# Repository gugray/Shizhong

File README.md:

# Remarkably Accurate Quartz Clock

This repository has all the code and design files for the Remarkably Accurate Quartz Clock
[documented on Hackaday](https://hackaday.io/project/190063-remarkably-accurate-quartz-clock).

Can I use cheap, everyday components and build a quartz clock that beats specialized RTCs and matches the best commercial timepieces? Let's find out!

32kHz quartz crystals typically have a ±20ppm (parts per million) frequency tolerance, which translates to drift potentially in excess of 10 minutes per year. Specialized RTCs like DS3231 promise ±2ppm, or about ±1 minute per year.

RAQC aims for drift below 10 seconds per year. To achieve this, it implements fine-grained frequency correction in software. It has a screen to adjust time with subsecond precision, and it measures the temperature at 10-minute intervals to compensate for dynamic drift. After calibrating repeatedly at incresingly long intervals, RAQC knows the crystal's static error with a 0.01ppm precision.

Energy-saving programming techniques and a low-power LCD display keep the clock's current draw under 15μA, promising 1.5 years of uptime on a CR2032 coin cell.

## Electronics

The KiCad 5.1.9 schematic and PCB are in [/electronics](electronics). The ZIP file there is the Gerber export that I submitted to the PCB fab.

## Laser-cut frame

The frame is laser-cut from 3mm acryclic; the top and bottom covers are 1mm transparent acrylic. The front panel with the engraved overview of the clock's menu is laser-cut from 2mm birch.
The vector files for this are in [/design](design). The .ai file is the original, but I included a version re-saved as Inkscape .svg as well.

## Source code

The source code is in [/code/board](code/board). I developed it using the [PlatformIO extension](https://platformio.org/install/ide?install=vscode) for Visual Studio Code, so if you want to explore the code and build it yourself, that might be the easiest way to get started. The code uses the Arduino framework. It has only one dependency, the Wire library for I2C communication.

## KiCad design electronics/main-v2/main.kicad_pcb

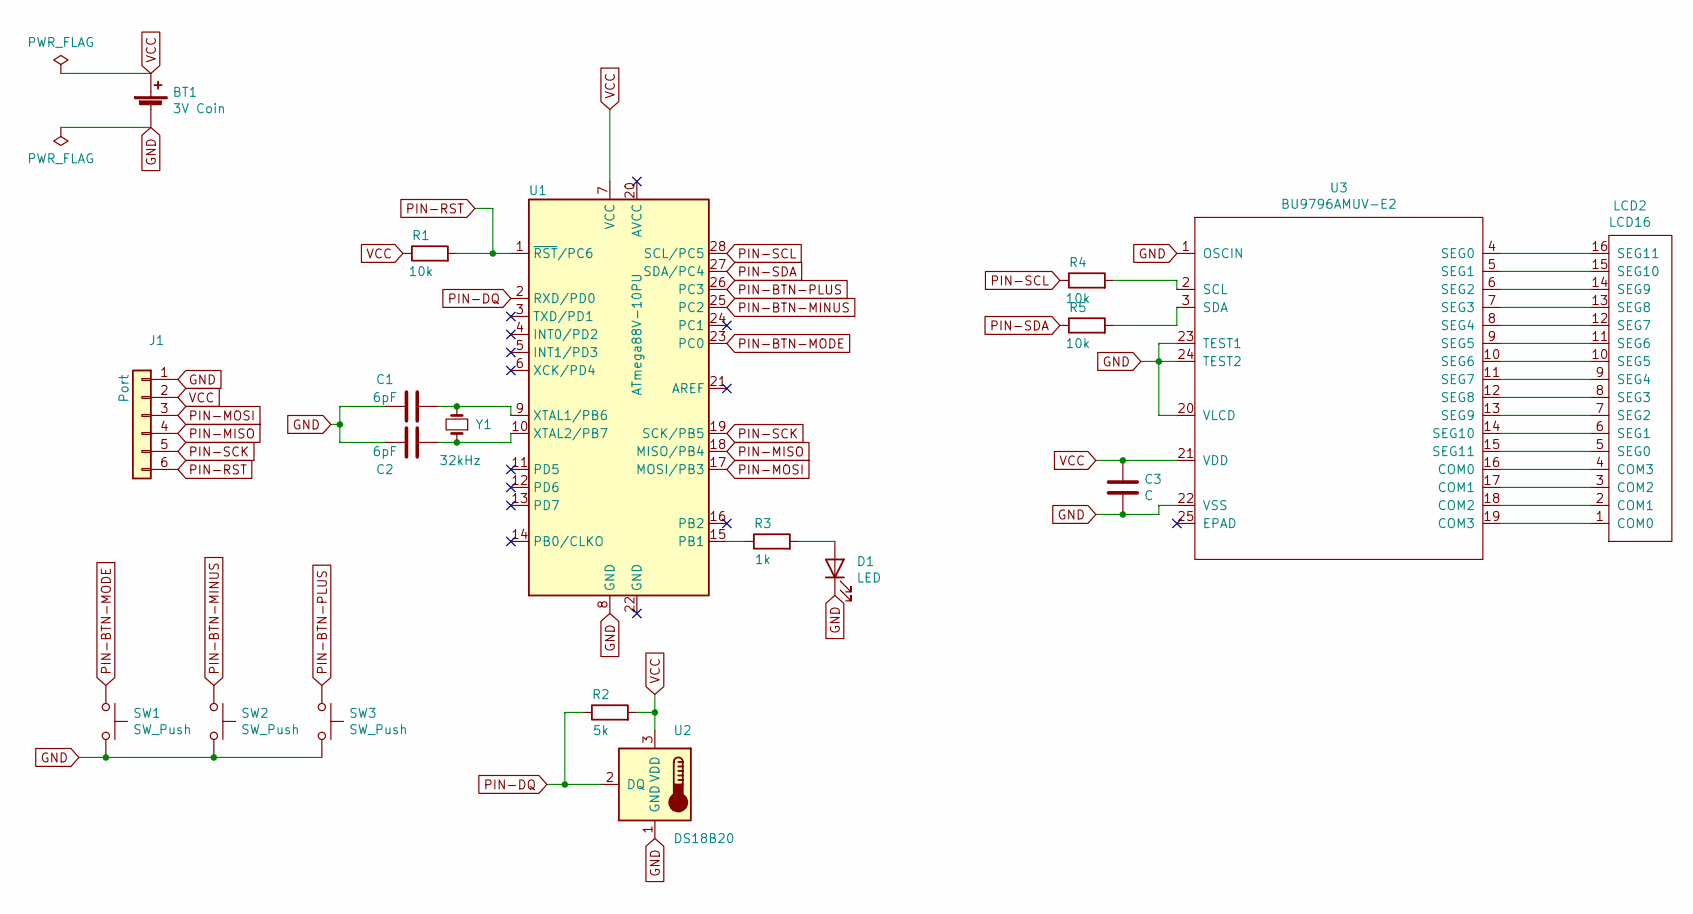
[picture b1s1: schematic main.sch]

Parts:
BT1: 3V Coin; BatteryHolder_Keystone_3002_1x2032
C1, C2: 6pF; R_Axial_DIN0204_L3.6mm_D1.6mm_P2.54mm_Vertical
C3: C; C_0603_1608Metric
D1: LED; LED_D2.0mm_W4.0mm_H2.8mm_FlatTop
J1: Port; PinHeader_1x06_P2.54mm_Vertical
LCD2: LCD16; LCD16-TN6
R1, R4, R5: 10k; R_Axial_DIN0207_L6.3mm_D2.5mm_P10.16mm_Horizontal
R2: 5k; R_Axial_DIN0207_L6.3mm_D2.5mm_P10.16mm_Horizontal
R3: 1k; R_Axial_DIN0207_L6.3mm_D2.5mm_P10.16mm_Horizontal
SW1, SW2, SW3: SW_Push; PushButton5mm
U1: ATmega88V-10PU; DIP-28_W7.62mm
U2: DS18B20; TO-92_Inline_Wide
U3: BU9796AMUV-E2; VQFN-24-1EP_4x4mm_P0.5mm_EP2.45x2.45mm
Y1: 32kHz; Crystal_C38-LF_D3.0mm_L8.0mm_Horizontal

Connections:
GND: BT1.2 (-), C1.1, C2.1, C3.2, D1.1 (K), J1.1, SW1.2, SW2.2, SW3.2, U1.8 (GND), U2.1 (GND), U3.1 (OSCIN), U3.20 (VLCD), U3.22 (VSS), U3.23 (TEST1), U3.24 (TEST2)
unnamed 1: C1.2, U1.9 (XTAL1/PB6), Y1.2; also elsewhere on the board
unnamed 2: C2.2, U1.10 (XTAL2/PB7), Y1.1; also elsewhere on the board
unnamed: D1.2 (A), R3.2
unnamed: LCD2.1 (COM0), U3.19 (COM3)
unnamed: LCD2.2 (COM1), U3.18 (COM2)
unnamed: LCD2.3 (COM2), U3.17 (COM1)
unnamed: LCD2.4 (COM3), U3.16 (COM0)
unnamed: LCD2.5 (SEG0), U3.15 (SEG11)
unnamed: LCD2.6 (SEG1), U3.14 (SEG10)
unnamed: LCD2.7 (SEG2), U3.13 (SEG9)
unnamed: LCD2.8 (SEG3), U3.12 (SEG8)
unnamed: LCD2.9 (SEG4), U3.11 (SEG7)
unnamed: LCD2.10 (SEG5), U3.10 (SEG6)
unnamed: LCD2.11 (SEG6), U3.9 (SEG5)
unnamed: LCD2.12 (SEG7), U3.8 (SEG4)
unnamed: LCD2.13 (SEG8), U3.7 (SEG3)
unnamed: LCD2.14 (SEG9), U3.6 (SEG2)
unnamed: LCD2.15 (SEG10), U3.5 (SEG1)
unnamed: LCD2.16 (SEG11), U3.4 (SEG0)
unnamed: R3.1, U1.15 (PB1)
unnamed: R4.2, U3.2 (SCL)
unnamed: R5.2, U3.3 (SDA)
PIN-BTN-MINUS: SW2.1, U1.25 (PC2)
PIN-BTN-MODE: SW1.1, U1.23 (PC0)
PIN-BTN-PLUS: SW3.1, U1.26 (PC3)
PIN-DQ: R2.1, U1.2 (RXD/PD0), U2.2 (DQ)
PIN-MISO: J1.4, U1.18 (MISO/PB4)
PIN-MOSI: J1.3, U1.17 (MOSI/PB3)
PIN-RST: J1.6, R1.2, U1.1 (~RST~/PC6)
PIN-SCK: J1.5, U1.19 (SCK/PB5)
PIN-SCL: R4.1, U1.28 (SCL/PC5)
PIN-SDA: R5.1, U1.27 (SDA/PC4)
VCC: BT1.1 (+), C3.1, J1.2, R1.1, R2.2, U1.7 (VCC), U2.3 (VDD), U3.21 (VDD)

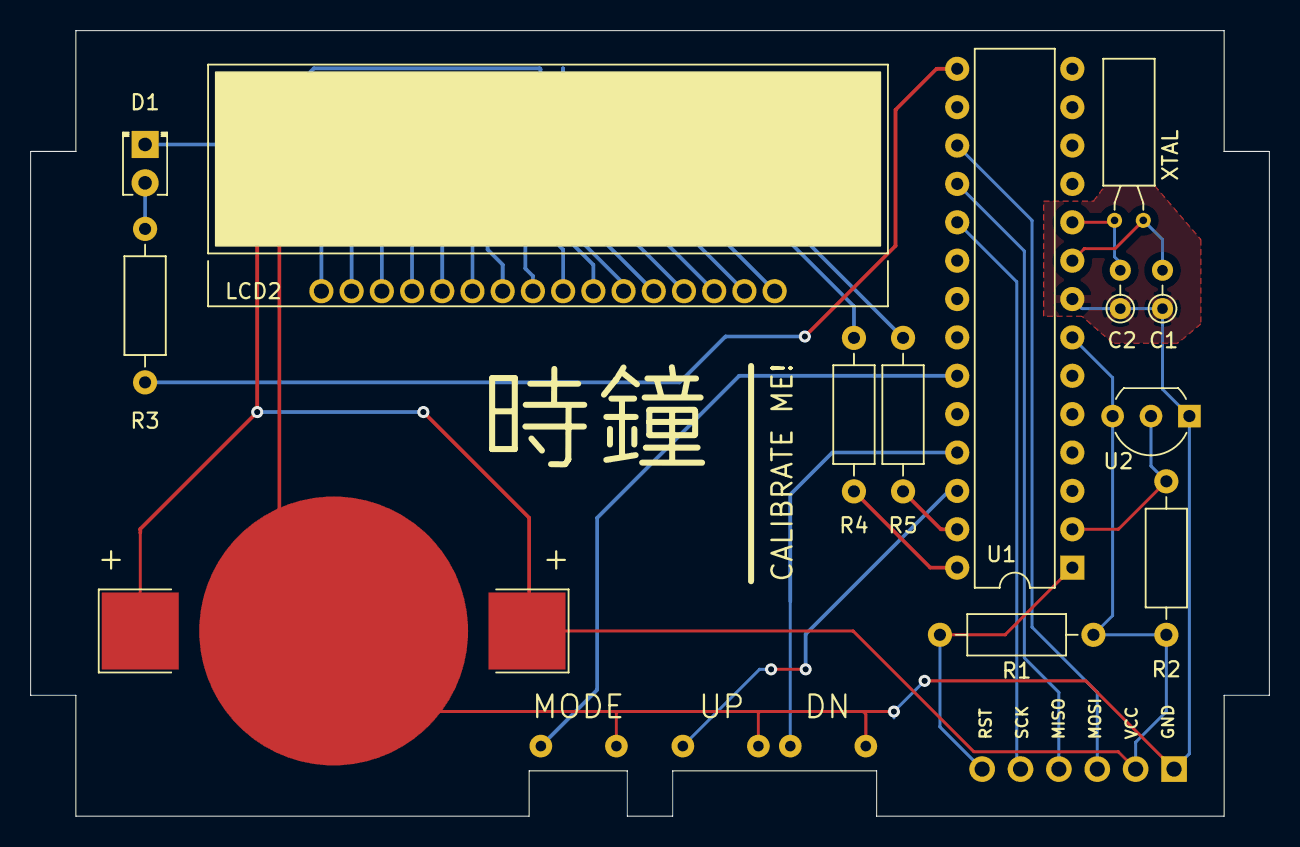
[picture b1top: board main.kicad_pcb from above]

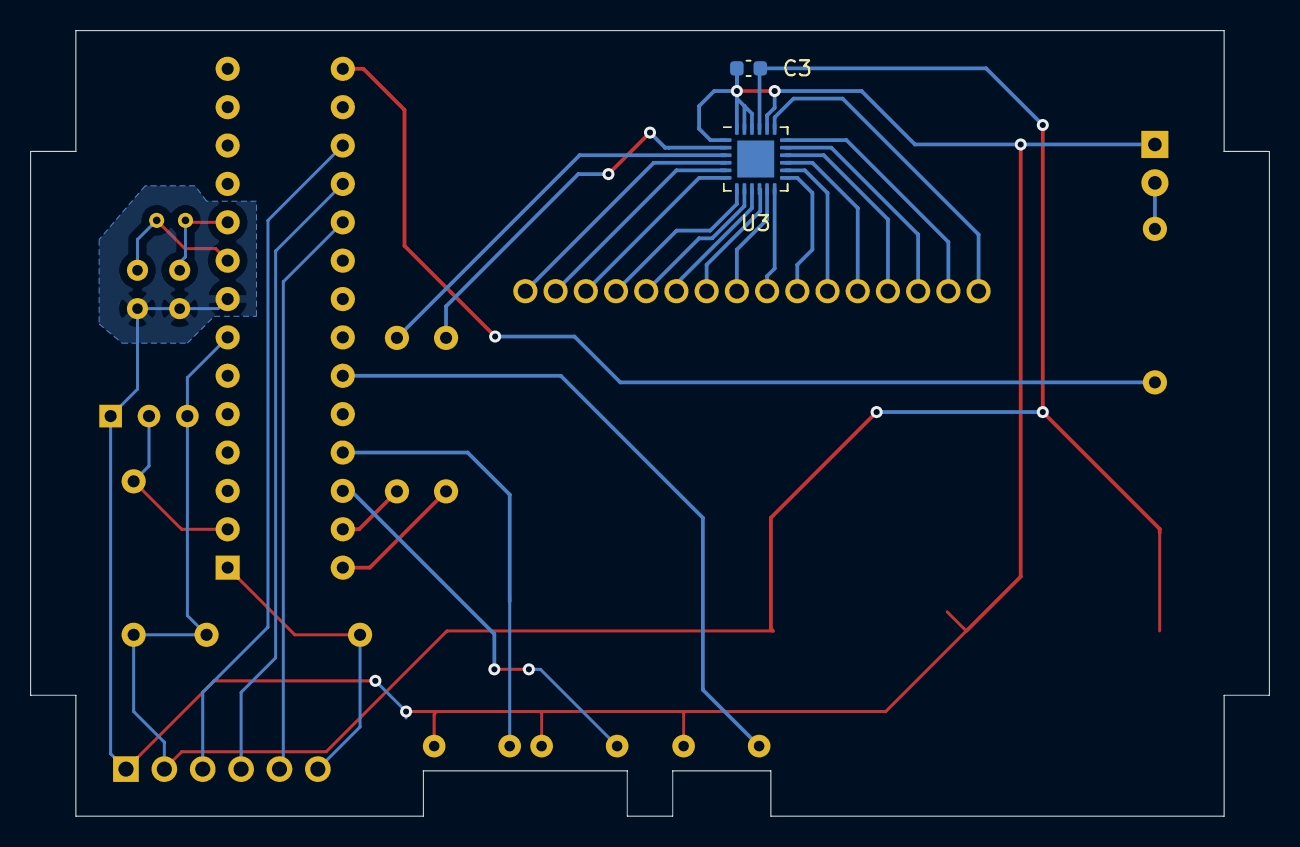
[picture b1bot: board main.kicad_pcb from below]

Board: 2 copper layers, 82.0 x 52.0 mm, 19 parts (2 on the bottom side), 34 nets.

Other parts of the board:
XTAL: 32kHz; Crystal_C38-LF_D3.0mm_L8.0mm_Horizontal

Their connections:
unnamed 1: XTAL.2; also elsewhere on the board
unnamed 2: XTAL.1; also elsewhere on the board

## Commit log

2023-02-26 clocklike behavior
2023-02-27 buttons handled
2023-02-27 optimized lcd update in clock; structuring code
2023-02-28 auto match counter recent - timer2 usage cleaner this way
2023-02-28 debounced buttons + quick tick thru timer 0
2023-02-28 fully clock, with working set_face
2023-03-01 revised time face + set face; stub tune face
2023-03-02 finetune working!
2023-03-03 temperature's working!
2023-03-03 static correction working!
2023-03-04 ofc i got sign & magnitude wrong
2023-03-04 two board variants
2023-03-05 nah formula was right, just can't insert a single extra beat at a time
2023-03-05 boards
2023-03-06 fix: extra tick in next period when second was lengthened
2023-03-06 only one face function; enter is an event too
2023-03-06 application note about calibration of STM32
2023-03-06 dynamic correction
2023-03-06 clearer formulation of, er, formula
2023-03-19 cleanup: electronics files
2023-03-19 design files for laser-cut case
2023-03-19 LED pin change for final PCB
2023-03-19 add pcb image
2023-03-19 update pcb image
2023-03-20 add final photo
2023-03-21 added uptime
